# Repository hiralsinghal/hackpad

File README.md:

# Hiral's Hackpad

This is a nine-key macropad with an OLED and two LEDs.

## Schematic

## PCB

## Case

## BOM

I will make this using:
- 9x Cherry MX Switches
- 9x DSA Keycaps
- 9x 1N4148 DO-35 Diodes
- 2x SK6812MINI-E LEDs
- 1x 0.91" 128x32 OLED Display
- 1x XIAO RP2040
- 1x Case (2 printed parts)

| Designator | Footprint | Quantity | Value | 
| ------ | ------ |------| ------ |
| D1, D2 | MX_SK6812MINI-E_REV | 2 | SK6812MINI-E |
| D10, D11, D3, D4, D5, D6, D7, D8, D9 | D_DO-35_SOD27_P7.62mm_Horizontal | 9 | 1N4148 |
| SW1, SW2, SW3, SW4, SW5, SW6, SW7, SW8, SW9 | SW_Cherry_MX_1.00u_PCB | 9 | SW_Push |
| U1 | OLED_0.91_128x32 | 1 | OLED_0.91_128x32 |
| U2 | XIAO-RP2040-DIP | 1 | XIAO-RP2040-DIP |

## Intent

I made this to delve into the world of hardware for the first time. I've never made something like this before. I am quite excited to build it and use it.

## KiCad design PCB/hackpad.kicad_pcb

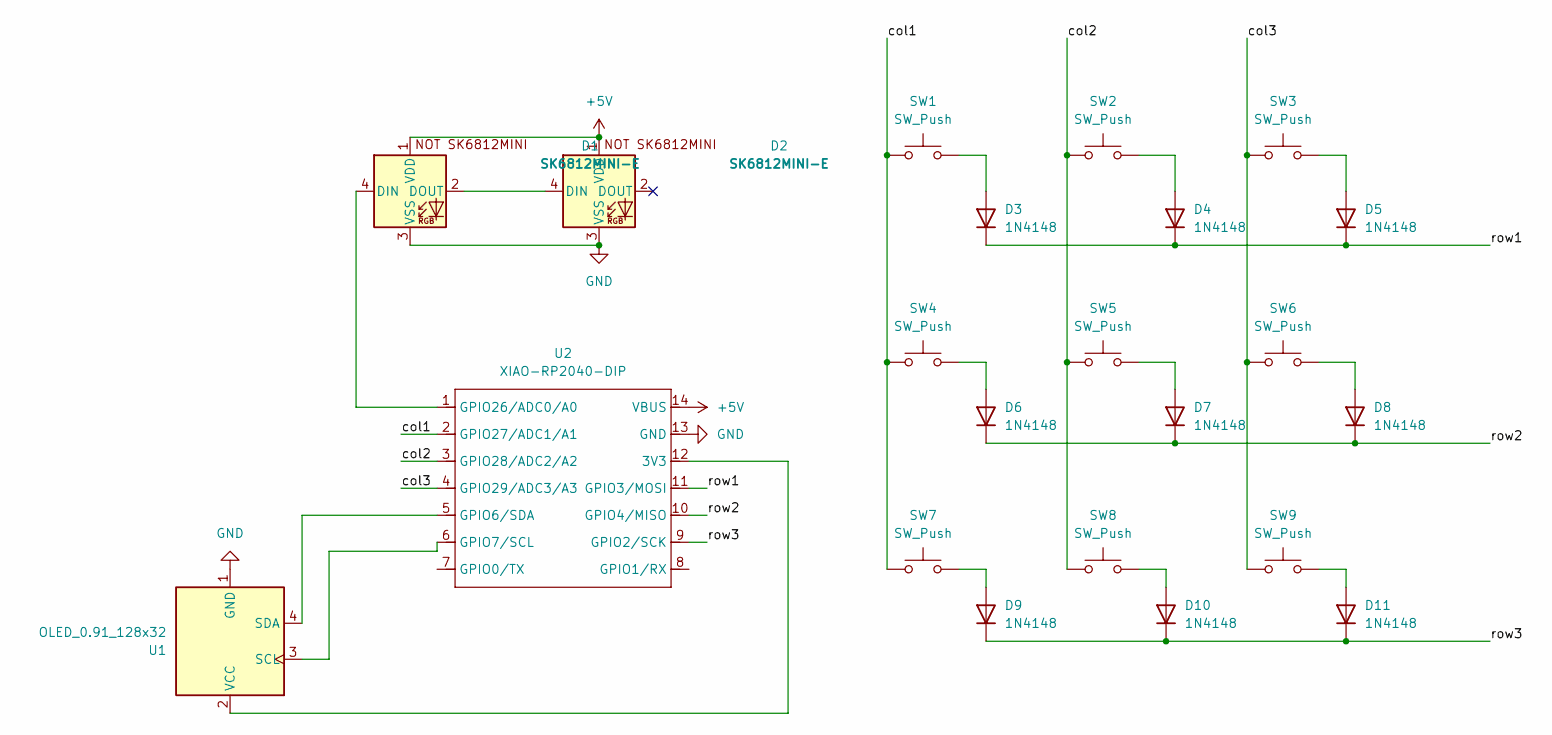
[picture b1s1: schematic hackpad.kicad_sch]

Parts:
D1, D2: SK6812MINI-E; MX_SK6812MINI-E_REV
D3, D4, D5, D6, D7, D8, D9, D10, D11: 1N4148; D_DO-35_SOD27_P7.62mm_Horizontal
SW1, SW2, SW3, SW4, SW5, SW6, SW7, SW8, SW9: SW_Push; SW_Cherry_MX_1.00u_PCB
U1: OLED_0.91_128x32
U2: XIAO-RP2040-DIP

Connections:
+5V: D1.1 (VDD), D2.1 (VDD), U2.14 (VBUS)
/col1: SW1.1, SW4.1, SW7.1, U2.2 (GPIO27/ADC1/A1)
/col2: SW2.1, SW5.1, SW8.1, U2.3 (GPIO28/ADC2/A2)
/col3: SW3.1, SW6.1, SW9.1, U2.4 (GPIO29/ADC3/A3)
/row1: D3.1 (K), D4.1 (K), D5.1 (K), U2.11 (GPIO3/MOSI)
/row2: D6.1 (K), D7.1 (K), D8.1 (K), U2.10 (GPIO4/MISO)
/row3: D9.1 (K), D10.1 (K), D11.1 (K), U2.9 (GPIO2/SCK)
GND: D1.3 (VSS), D2.3 (VSS), U1.1 (GND), U2.13 (GND)
unnamed: D1.4 (DIN), U2.1 (GPIO26/ADC0/A0)
unnamed: D1.2 (DOUT), D2.4 (DIN)
unnamed: D3.2 (A), SW1.2
unnamed: D4.2 (A), SW2.2
unnamed: D5.2 (A), SW3.2
unnamed: D6.2 (A), SW4.2
unnamed: D7.2 (A), SW5.2
unnamed: D8.2 (A), SW6.2
unnamed: D9.2 (A), SW7.2
unnamed: D10.2 (A), SW8.2
unnamed: D11.2 (A), SW9.2
unnamed: U1.3 (SCL), U2.6 (GPIO7/SCL)
unnamed: U1.4 (SDA), U2.5 (GPIO6/SDA)
unnamed: U1.2 (VCC), U2.12 (3V3)

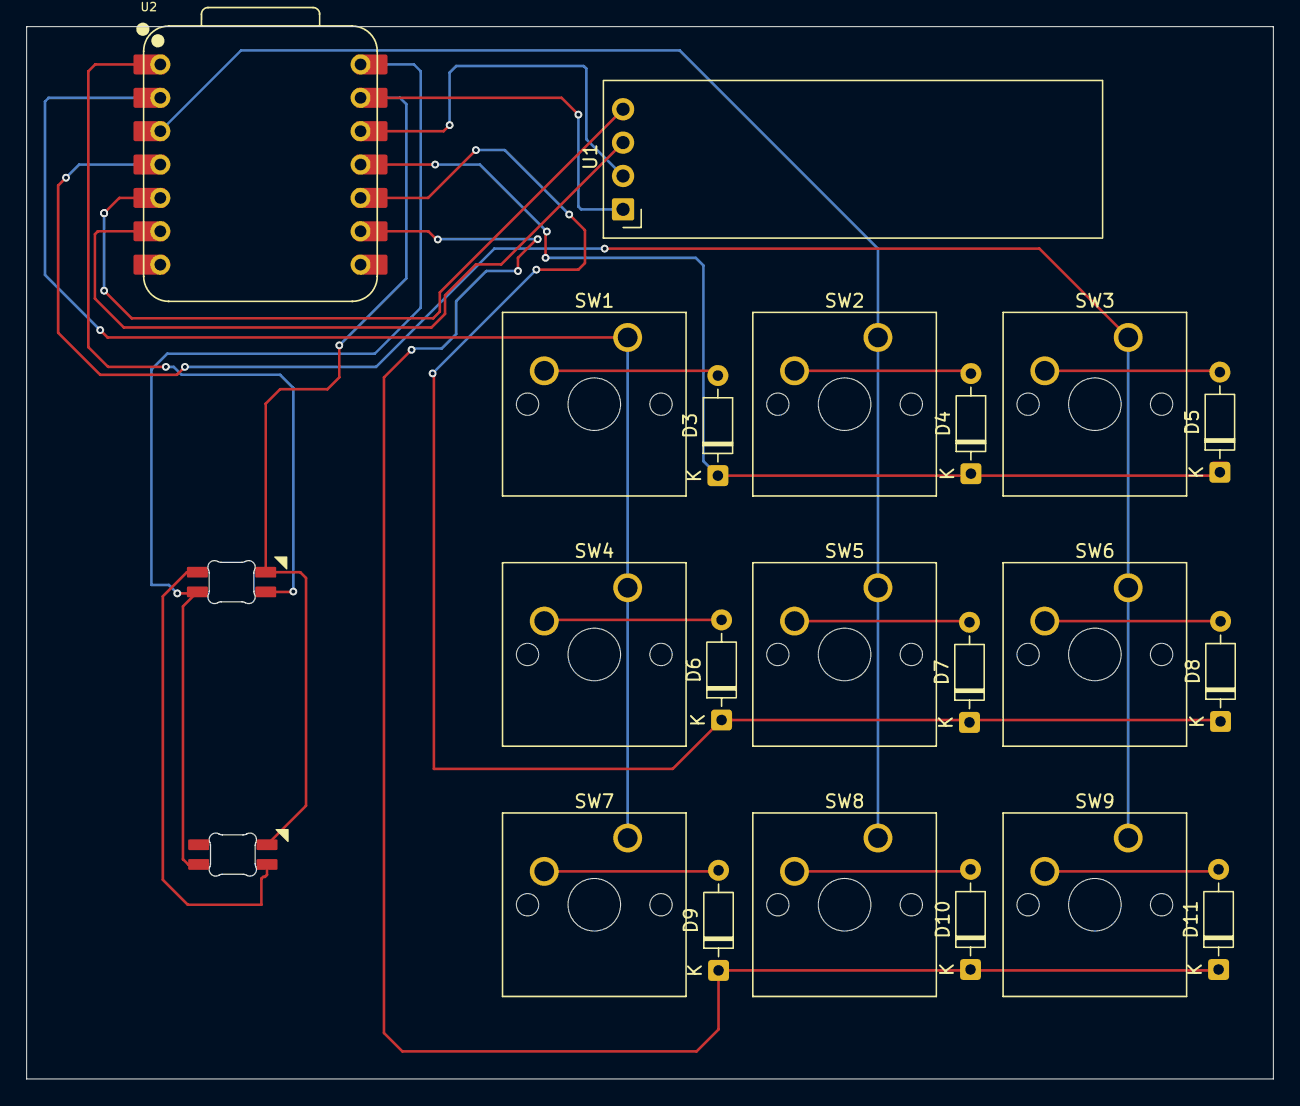
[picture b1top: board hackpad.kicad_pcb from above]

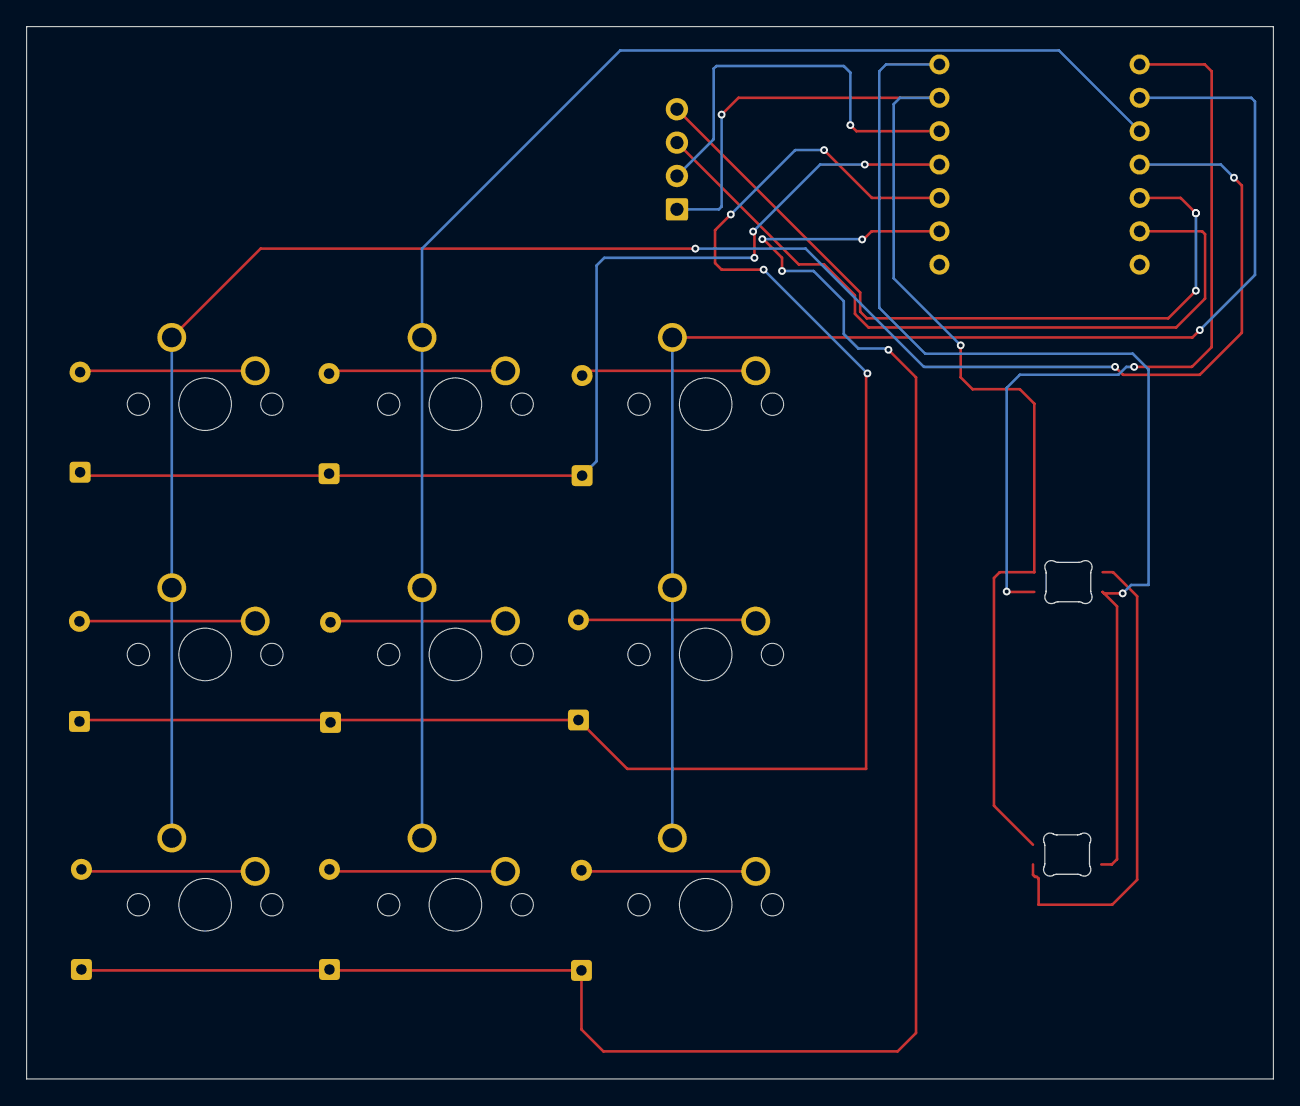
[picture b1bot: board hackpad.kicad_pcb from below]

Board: 2 copper layers, 94.9 x 80.1 mm, 22 parts (2 on the bottom side), 22 nets.

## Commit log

2026-02-25 My hackpad!!
2026-02-26 update cad, readme
